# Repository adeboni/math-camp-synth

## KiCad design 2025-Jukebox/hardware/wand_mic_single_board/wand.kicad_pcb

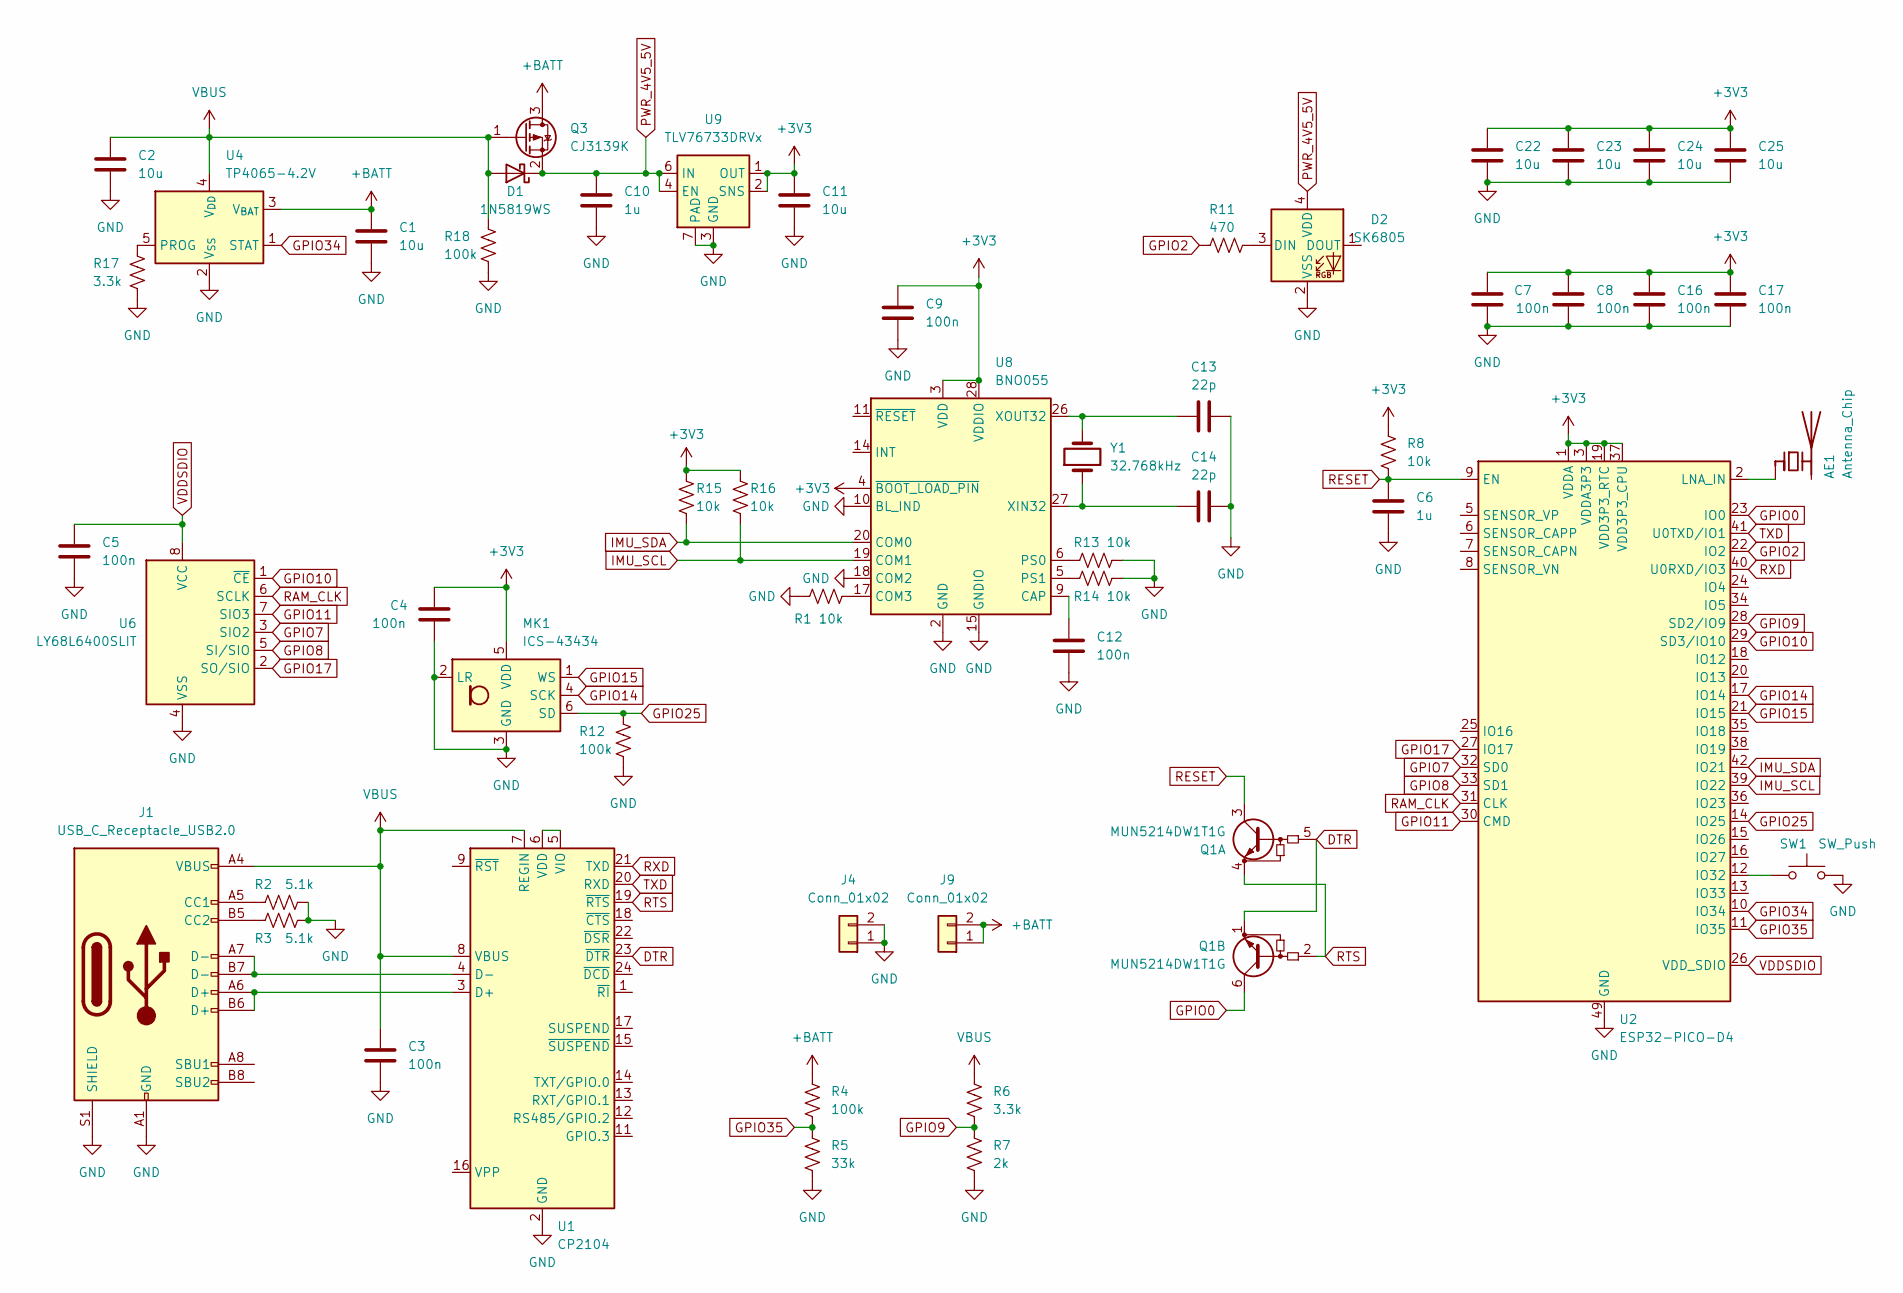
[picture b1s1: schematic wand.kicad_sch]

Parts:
AE1: Antenna_Chip; C_1206_3216Metric_Pad1.33x1.80mm_HandSolder
C1, C2, C11, C22, C23, C24, C25: 10u; C_0402_1005Metric
C3, C4, C5, C7, C8, C9, C12, C16, C17: 100n; C_0402_1005Metric
C6, C10: 1u; C_0402_1005Metric
C13, C14: 22p; C_0402_1005Metric
D1: 1N5819WS; D_SOD-323
D2: SK6805; LED_SK6805_PLCC4_2.4x2.7mm_P1.3mm
J1: USB_C_Receptacle_USB2.0; USB_C_Receptacle_Palconn_UTC16-G
J4, J9: Conn_01x02; PinHeader_1x02_P2.54mm_Vertical
MK1: ICS-43434; InvenSense_ICS-43434-6_3.5x2.65mm
Q1: MUN5214DW1T1G; SOT-363_SC-70-6
Q3: CJ3139K; SOT-723
R1, R8, R13, R14, R15, R16: 10k; R_0402_1005Metric
R2, R3: 5.1k; R_0402_1005Metric
R4, R12, R18: 100k; R_0402_1005Metric
R5: 33k; R_0402_1005Metric
R6, R17: 3.3k; R_0402_1005Metric
R7: 2k; R_0402_1005Metric
R11: 470; R_0402_1005Metric
SW1: SW_Push; SW_PUSH_6mm_H13mm
U1: CP2104; QFN-24-1EP_4x4mm_P0.5mm_EP2.6x2.6mm
U2: ESP32-PICO-D4; QFN-48-1EP_7x7mm_P0.5mm_EP5.3x5.3mm
U4: TP4065-4.2V; SOT-23-5
U6: LY68L6400SLIT; SOIC-8_3.9x4.9mm_P1.27mm
U8: BNO055; LGA-28_5.2x3.8mm_P0.5mm
U9: TLV76733DRVx; WSON-6-1EP_2x2mm_P0.65mm_EP1x1.6mm_ThermalVias
Y1: 32.768kHz; Crystal_SMD_3215-2Pin_3.2x1.5mm

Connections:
+3V3: C4.1, C7.1, C8.1, C9.1, C11.1, C16.1, C17.1, C22.1, C23.1, C24.1, C25.1, MK1.5 (VDD), R8.1, R15.1, R16.1, U2.1 (VDDA), U2.3 (VDDA3P3), U2.4 (VDDA3P3), U2.19 (VDD3P3_RTC), U2.37 (VDD3P3_CPU), U2.43 (VDDA), U2.46 (VDDA), U8.3 (VDD), U8.4 (~BOOT_LOAD_PIN), U8.28 (VDDIO), U9.1 (OUT), U9.2 (SNS)
+BATT: C1.1, J9.1, J9.2, Q3.3 (D), R4.1, U4.3 (V_{BAT})
DTR: Q1.1 (E2), Q1.5 (B1), U1.23 (~DTR)
GND: C1.2, C2.2, C3.2, C4.2, C5.2, C6.2, C7.2, C8.2, C9.2, C10.2, C11.2, C12.2, C13.2, C14.2, C16.2, C17.2, C22.2, C23.2, C24.2, C25.2, D2.2 (VSS), J1.A1 (GND), J1.A12 (GND), J1.B1 (GND), J1.B12 (GND), J1.S1 (SHIELD), J4.1, J4.2, MK1.2 (LR), MK1.3 (GND), R1.2, R2.2, R3.2, R5.2, R7.2, R12.2, R13.1, R14.1, R17.1, R18.1, SW1.2, U1.2 (GND), U1.25 (GND), U2.49 (GND), U4.2 (V_{SS}), U6.4 (VSS), U8.2 (GND), U8.10 (BL_IND), U8.15 (GNDIO), U8.16 (GNDIO), U8.18 (COM2), U8.25 (GNDIO), U9.3 (GND), U9.5 (GND), U9.7 (PAD)
GPIO0: Q1.6 (C2), U2.23 (IO0)
GPIO2: R11.2, U2.22 (IO2)
GPIO7: U2.32 (SD0), U6.3 (SIO2)
GPIO8: U2.33 (SD1), U6.5 (SI/SIO)
GPIO9: R6.2, R7.1, U2.28 (SD2/IO9)
GPIO10: U2.29 (SD3/IO10), U6.1 (~CE)
GPIO11: U2.30 (CMD), U6.7 (SIO3)
GPIO14: MK1.4 (SCK), U2.17 (IO14)
GPIO15: MK1.1 (WS), U2.21 (IO15)
GPIO17: U2.27 (IO17), U6.2 (SO/SIO)
GPIO25: MK1.6 (SD), R12.1, U2.14 (IO25)
GPIO34: U2.10 (IO34), U4.1 (STAT)
GPIO35: R4.2, R5.1, U2.11 (IO35)
IMU_SCL: R16.2, U2.39 (IO22), U8.19 (COM1)
IMU_SDA: R15.2, U2.42 (IO21), U8.20 (COM0)
unnamed: AE1.1 (FEED), U2.2 (LNA_IN)
unnamed: D2.3 (DIN), R11.1
unnamed: J1.A5 (CC1), R2.1
unnamed: J1.B5 (CC2), R3.1
unnamed: J1.A6 (D+), J1.B6 (D+), U1.3 (D+)
unnamed: J1.A7 (D-), J1.B7 (D-), U1.4 (D-)
unnamed: U1.5 (VIO), U1.6 (VDD)
unnamed: SW1.1, U2.12 (IO32)
unnamed: R17.2, U4.5 (PROG)
unnamed: C12.1, U8.9 (CAP)
unnamed: R1.1, U8.17 (COM3)
unnamed: R13.2, U8.6 (PS0)
unnamed: R14.2, U8.5 (PS1)
unnamed: C14.1, U8.27 (XIN32), Y1.1
unnamed: C13.1, U8.26 (XOUT32), Y1.2
PWR_4V5_5V: C10.1, D1.1 (K), D2.4 (VDD), Q3.2 (S), U9.4 (EN), U9.6 (IN)
RAM_CLK: U2.31 (CLK), U6.6 (SCLK)
RESET: C6.1, Q1.3 (C1), R8.2, U2.9 (EN)
RTS: Q1.2 (B2), Q1.4 (E1), U1.19 (~RTS)
RXD: U1.21 (TXD), U2.40 (U0RXD/IO3)
TXD: U1.20 (RXD), U2.41 (U0TXD/IO1)
VBUS: C2.1, C3.1, D1.2 (A), J1.A4 (VBUS), J1.A9 (VBUS), J1.B4 (VBUS), J1.B9 (VBUS), Q3.1 (G), R6.1, R18.2, U1.7 (REGIN), U1.8 (VBUS), U4.4 (V_{DD})
VDDSDIO: C5.1, U2.26 (VDD_SDIO), U6.8 (VCC)

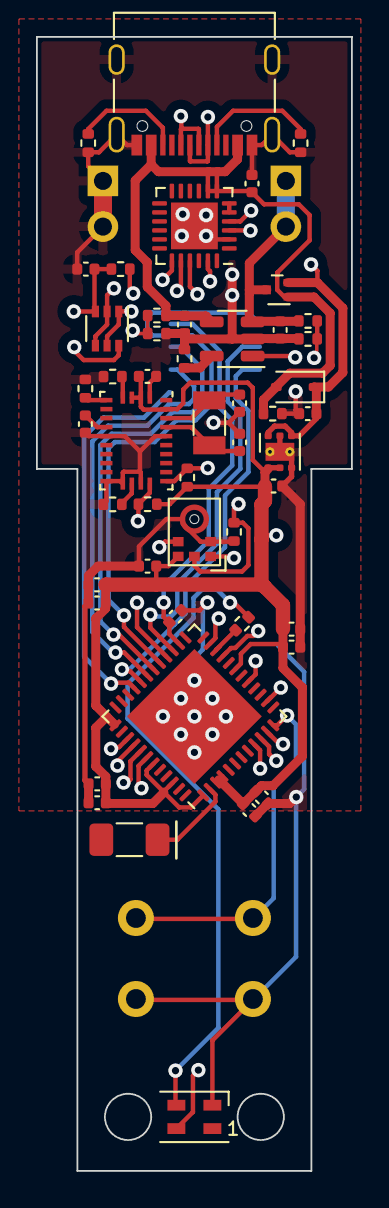
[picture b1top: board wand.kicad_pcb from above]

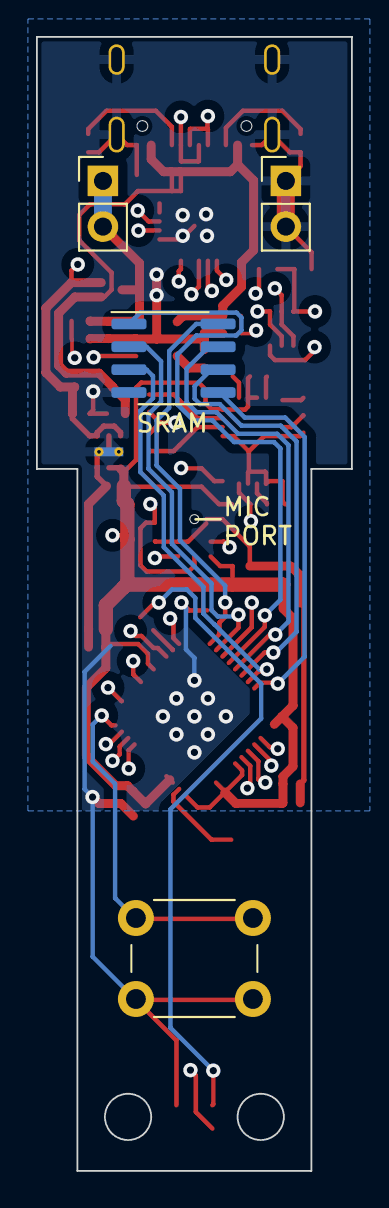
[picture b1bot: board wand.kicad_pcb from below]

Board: 4 copper layers, 17.5 x 63.0 mm, 53 parts (4 on the bottom side), 42 nets.

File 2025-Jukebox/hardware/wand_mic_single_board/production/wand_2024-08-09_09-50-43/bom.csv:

Designator,Footprint,Quantity,Value,LCSC Part #
AE1,1206,1,Antenna_Chip,C293767
"C1, C11, C2, C22, C23, C24, C25",0402,7,10u,C15525
"C10, C6",0402,2,1u,C52923
"C12, C16, C17, C3, C4, C5, C7, C8, C9",0402,9,100n,C307331
"C13, C14",0402,2,22p,C1555
D1,D_SOD-323,1,1N5819WS,C191023
D2,LED_SK6805_PLCC4_2.4x2.7mm_P1.3mm,1,SK6805,C2909056
J1,USB_C_Receptacle_Palconn_UTC16-G,1,USB_C_Receptacle_USB2.0,C2765186
MK1,InvenSense_ICS-43434-6_3.5x2.65mm,1,ICS-43434,C5656610
Q1,SOT-363_SC-70-6,1,MUN5214DW1T1G,C94403
Q3,SOT-723,1,CJ3139K,C70022
"R1, R13, R14, R15, R16, R8",0402,6,10k,C25744
R11,0402,1,470,C25117
"R12, R18, R4",0402,3,100k,C25741
"R17, R6",0402,2,3.3k,C25890
"R2, R3",0402,2,5.1k,C25905
R5,0402,1,33k,C25779
R7,0402,1,2k,C4109
U1,QFN-24-1EP_4x4mm_P0.5mm_EP2.6x2.6mm,1,CP2104,C47742
U2,QFN-48-1EP_7x7mm_P0.5mm_EP5.3x5.3mm,1,ESP32-PICO-D4,C193707
U4,SOT-23-5,1,TP4065-4.2V,C113540
U8,LGA-28_5.2x3.8mm_P0.5mm,1,BNO055,C93216
U9,WSON-6-1EP_2x2mm_P0.65mm_EP1x1.6mm_ThermalVias,1,TLV76733DRVx,C2848334
Y1,Crystal_SMD_3215-2Pin_3.2x1.5mm,1,32.768kHz,C32346
